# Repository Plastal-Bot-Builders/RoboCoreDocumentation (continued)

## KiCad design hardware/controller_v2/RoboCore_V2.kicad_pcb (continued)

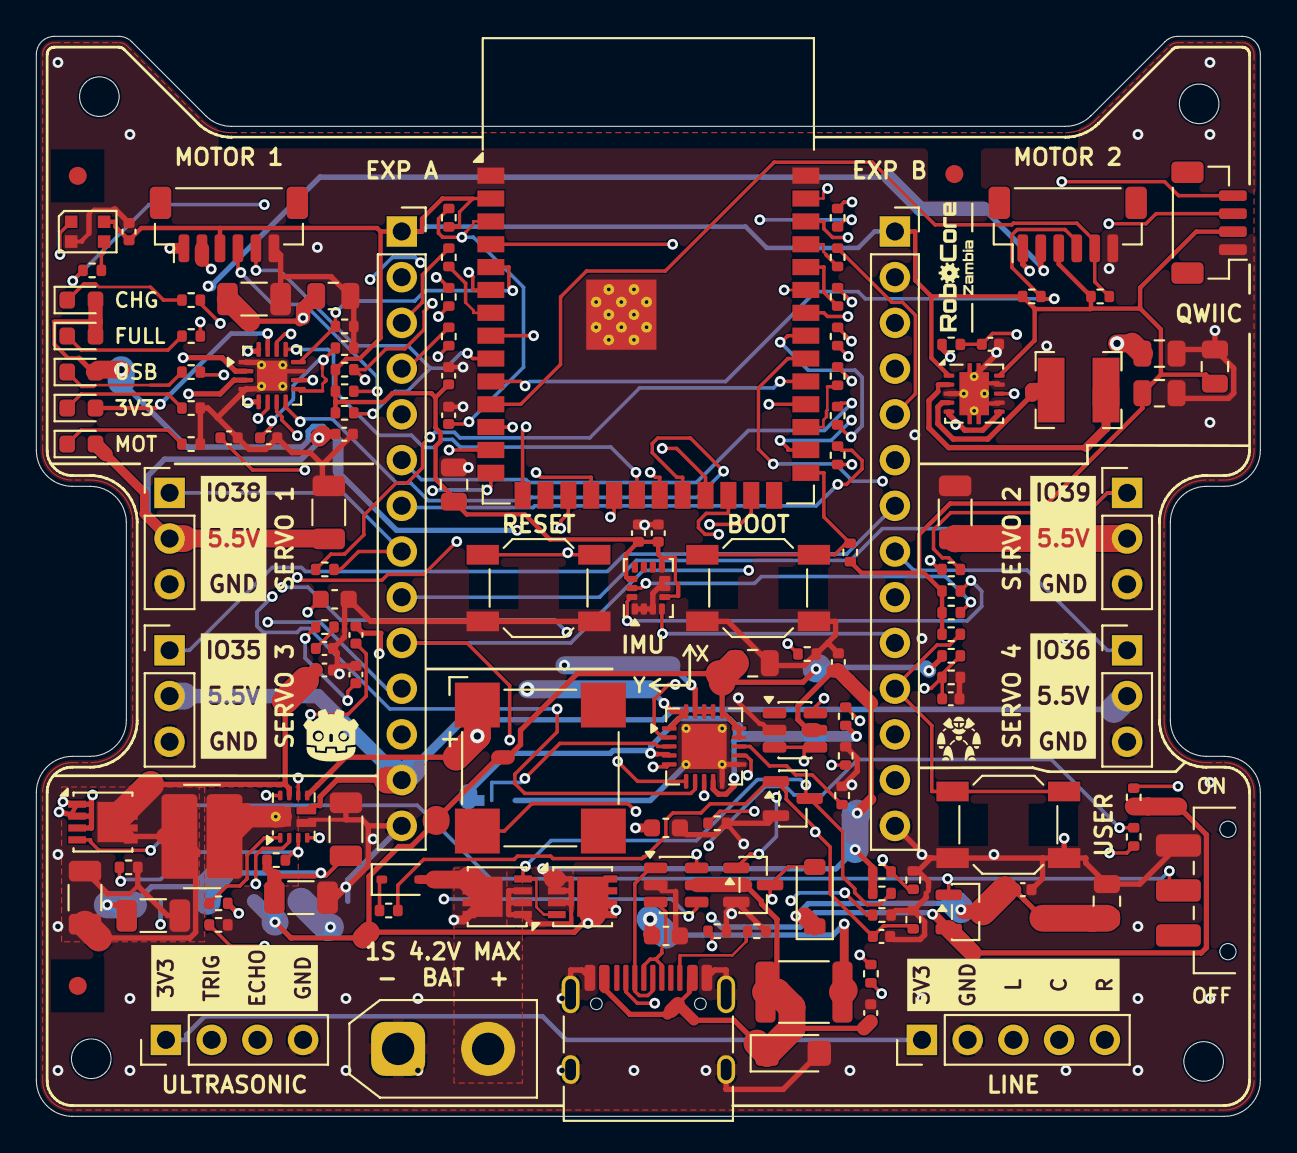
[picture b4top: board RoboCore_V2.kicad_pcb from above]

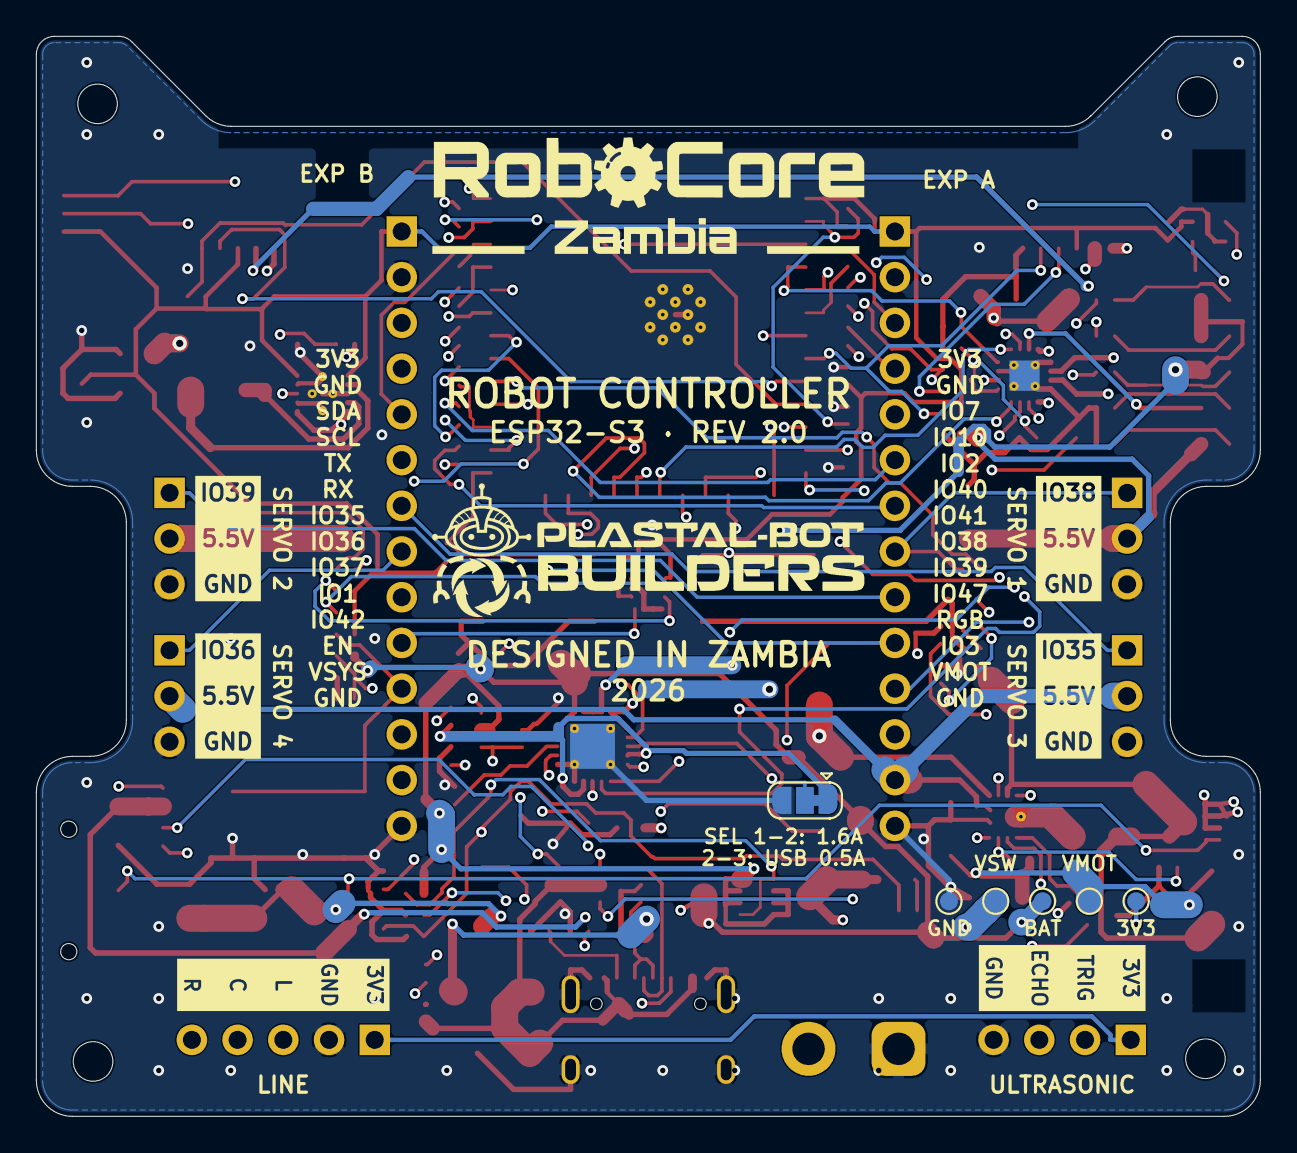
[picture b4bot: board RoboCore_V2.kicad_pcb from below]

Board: 4 copper layers, 68.0 x 60.0 mm, 146 parts (6 on the bottom side), 100 nets.

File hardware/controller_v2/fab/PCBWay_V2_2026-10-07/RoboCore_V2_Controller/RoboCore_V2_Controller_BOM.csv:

Item #,Designator,Qty,Manufacturer,Mfg Part #,Description / Value,Package/Footprint,Mounting Type,LCSC Part #,Notes
1,BZ201,1,Same Sky (CUI),CMT-8504-100-SMT-TR,Magnetic buzzer 8.5 mm (CMT-8504-100-SMT),MagneticBuzzer_CUI_CMT-8504-100-SMT,SMD,C22359707,"LCSC had only 12 (2026-10-07); Digi-Key has 30,000+."
2,"C101,C106,C107,C112,C114,C120,C122,C202,C204,C205,C206,C302",12,Samsung,CL05B104KB5NNNC,Ceramic capacitor 100nF 50V X7R ±10% 0402 (0.1uF),C_0402_1005Metric,SMD,C960916,
3,C102,1,Samsung,CL10A105KA8NNNC,Ceramic capacitor 1uF 25V X5R ±10% 0603 (1uF),C_0603_1608Metric,SMD,C5673,
4,C103,1,Samsung,CL10A106MO8NQNC,Ceramic capacitor 10uF 16V X5R ±20% 0603 (10uF),C_0603_1608Metric,SMD,C92487,
5,C104,1,Samsung,CL21A475KAQNNNE,Ceramic capacitor 4.7uF 25V X5R ±10% 0805 (4.7uF),C_0805_2012Metric,SMD,C1779,
6,"C105,C108,C301",3,Samsung,CL21A106KOQNNNE,Ceramic capacitor 10uF 16V X5R ±10% 0805 (10uF),C_0805_2012Metric,SMD,C1713,
7,"C109,C110,C201",3,Samsung,CL21A226MAQNNNE,Ceramic capacitor 22uF 25V X5R ±20% 0805 (22uF),C_0805_2012Metric,SMD,C45783,
8,"C111,C117,C118,C119,C303,C401,C402",7,Samsung,CL31A226KAHNNNE,Ceramic capacitor 22uF 25V X5R ±10% 1206 (22uF),C_1206_3216Metric,SMD,C12891,
9,C113,1,Samsung,CL10A225KO8NNNC,Ceramic capacitor 2.2uF 16V X5R ±10% 0603 (2.2uF),C_0603_1608Metric,SMD,C23630,
10,C115,1,Samsung,CL05B103KB5NNNC,Ceramic capacitor 10nF 50V X7R ±10% 0402 (10nF),C_0402_1005Metric,SMD,C15195,
11,C116,1,Samsung,CL05C220JB5NNNC,Ceramic capacitor 22pF 50V C0G ±5% 0402 (22pF),C_0402_1005Metric,SMD,C70464,
12,"C121,C203",2,Samsung,CL05A105KA5NNNC,Ceramic capacitor 1uF 25V X5R ±10% 0402 (1uF),C_0402_1005Metric,SMD,C16193167,
13,"C304,C305",2,Samsung,CL05B102KB5NNNC,Ceramic capacitor 1nF 50V X7R ±10% 0402 (1nF),C_0402_1005Metric,SMD,C14442,
14,"D101,D105",2,Lite-On,LTST-C191KRKT,LED red 0603 (RED),LED_0603_1608Metric,SMD,C125099,
15,"D102,D104",2,Lite-On,LTST-C191KGKT,LED green 0603 (GREEN),LED_0603_1608Metric,SMD,C125098,
16,D103,1,Lite-On,LTST-C191TBKT,LED blue 0603 (BLUE),LED_0603_1608Metric,SMD,C99290,
17,D106,1,Littelfuse,SMF5.0A,TVS diode 5 V (SMF5.0A),D_SMF,SMD,C151296,
18,D107,1,Vishay,1N4148WS-E3-08,Switching diode (1N4148WS),D_SOD-323,SMD,C129905,
19,D201,1,Worldsemi,WS2812B-2020-V6,Addressable RGB LED 2020 (WS2812B-2020),LED_WS2812B-2020_PLCC4_2.0x2.0mm,SMD,C52917434,
20,D202,1,Diodes Inc,1N4148W-7-F,Switching diode (1N4148W),D_SOD-123,SMD,C83528,
21,F101,1,Bourns,MF-MSMF150/24X-2,PTC resettable fuse 1.5 A (1.5A),Fuse_1812_4532Metric,SMD,C78695,
22,J101,1,HRO,TYPE-C-31-M-12,"USB-C receptacle, 16 pin (TYPE-C-31-M-12)",USB_C_Receptacle_HRO_TYPE-C-31-M-12,SMD,C165948,
23,J102,1,AMASS,XT30UPB-M,"Battery connector XT30, male, vertical (XT30UPB-M)",AMASS_XT30UPB-M_1x02_P5.0mm_Vertical,THT,C428721,"Through-hole, top side."
24,"J201,J403",2,JST,BM04B-SRSS-TB,JST SH 4-pin vertical header (Qwiic / ULTRASONIC),JST_SH_BM04B-SRSS-TB_1x04-1MP_P1.00mm_Vertical,SMD,C160390,
25,"J301,J302",2,JST,BM06B-SRSS-TB,JST SH 6-pin vertical header (MOTOR_1 / MOTOR_2),JST_SH_BM06B-SRSS-TB_1x06-1MP_P1.00mm_Vertical,SMD,C160392,
26,"J401,J402,J407,J408",4,hanxia,HX PH254-01-03-Z-L11.5,"Pin header 1x3, 2.54 mm, straight (SERVO_1 / SERVO_2 / SERVO_3 / SERVO_4)",PinHeader_1x03_P2.54mm_Vertical,THT,C52016391,"Through-hole, top side, short end in the board (6 mm pin up)."
27,J404,1,JST,BM05B-SRSS-TB,JST SH 5-pin vertical header (LINE_FOLLOWER),JST_SH_BM05B-SRSS-TB_1x05-1MP_P1.00mm_Vertical,SMD,C160391,
28,"J405,J406",2,Hong Cheng,HC-PM254-8.5H-1x14PZ,"Female socket 1x14, 2.54 mm, 8.5 mm tall (EXPANSION_A / EXPANSION_B)",PinSocket_1x14_P2.54mm_Vertical,THT,C22373900,"Through-hole, top side."
29,L101,1,Bourns,SRN4018-2R2M,Power inductor 2.2 uH (2.2uH),L_Bourns-SRN4018,SMD,C913207,
30,L102,1,Bourns,SRP5030CA-2R2M,Power inductor 2.2 uH (2.2uH),L_Bourns_SRP5030CA,SMD,C2046809,
31,Q101,1,Alpha & Omega,AO3401A,P-channel MOSFET 30 V (AO3401A),SOT-23,SMD,C15127,
32,"Q102,Q103,Q104",3,Vishay,SI7655DN-T1-GE3,"P-channel MOSFET, PowerPAK 1212-8 (SI7655DN)",Vishay_PowerPAK_1212-8_Single,SMD,C727830,
33,"Q105,Q201",2,Alpha & Omega,AO3400A,N-channel MOSFET 30 V (AO3400A),SOT-23,SMD,C20917,
34,"R101,R102",2,UNI-ROYAL,0402WGF5101TCE,Chip resistor 5.1kΩ ±1% 0402 (5.1k),R_0402_1005Metric,SMD,C25905,
35,"R103,R106,R201,R202,R203,R303,R304,R305,R306,R307",10,UNI-ROYAL,0402WGF1002TCE,Chip resistor 10kΩ ±1% 0402 (10k),R_0402_1005Metric,SMD,C25744,
36,R104,1,UNI-ROYAL,0402WGF2673TCE,Chip resistor 267kΩ ±1% 0402 (267k),R_0402_1005Metric,SMD,C270622,
37,"R105,R107,R108,R109,R119",5,YAGEO,RC0402FR-071KL,Chip resistor 1kΩ ±1% 0402 (1k),R_0402_1005Metric,SMD,C106235,
38,"R110,R117,R118,R121,R122,R123,R206",7,UNI-ROYAL,0402WGF1003TCE,Chip resistor 100kΩ ±1% 0402 (100k),R_0402_1005Metric,SMD,C25741,
39,"R111,R205",2,YAGEO,RC0402FR-07100RL,Chip resistor 100Ω ±1% 0402 (100),R_0402_1005Metric,SMD,C106232,
40,R112,1,UNI-ROYAL,0402WGF9101TCE,Chip resistor 9.1kΩ ±1% 0402 (9.1k),R_0402_1005Metric,SMD,C25926,
41,"R113,R115",2,UNI-ROYAL,0402WGF3003TCE,Chip resistor 300kΩ ±1% 0402 (300k),R_0402_1005Metric,SMD,C25774,
42,R114,1,UNI-ROYAL,0402WGF8452TCE,Chip resistor 84.5kΩ ±1% 0402 (84.5k),R_0402_1005Metric,SMD,C26988,
43,R116,1,UNI-ROYAL,0402WGF2003TCE,Chip resistor 200kΩ ±1% 0402 (200k),R_0402_1005Metric,SMD,C25764,
44,R120,1,UNI-ROYAL,0402WGF2201TCE,Chip resistor 2.2kΩ ±1% 0402 (2.2k),R_0402_1005Metric,SMD,C25879,
45,R124,1,UNI-ROYAL,0402WGF3303TCE,Chip resistor 330kΩ ±1% 0402 (330k),R_0402_1005Metric,SMD,C25778,
46,R125,1,UNI-ROYAL,0402WGF1004TCE,Chip resistor 1MΩ ±1% 0402 (1M),R_0402_1005Metric,SMD,C26083,
47,R126,1,UNI-ROYAL,0402WGF9532TCE,Chip resistor 95.3kΩ ±1% 0402 (95.3k),R_0402_1005Metric,SMD,C26990,
48,R204,1,YAGEO,RC0402FR-0733RL,Chip resistor 33Ω ±1% 0402 (33),R_0402_1005Metric,SMD,C138002,
49,"R207,R208",2,UNI-ROYAL,0402WGF4701TCE,Chip resistor 4.7kΩ ±1% 0402 (4.7k),R_0402_1005Metric,SMD,C25900,
50,"R301,R302",2,UNI-ROYAL,0402WGF1652TCE,Chip resistor 16.5kΩ ±1% 0402 (16.5k),R_0402_1005Metric,SMD,C25857,
51,"R401,R402,R403,R404,R405,R406,R407,R408,R409,R410,R411,R412,R413",13,UNI-ROYAL,0402WGF3300TCE,Chip resistor 330Ω ±1% 0402 (330),R_0402_1005Metric,SMD,C25104,
52,SW101,1,C&K,JS102011SAQN,"Slide switch SPDT, side-actuated (ON/OFF)",SW_SPDT_CK_JS102011SAQN,SMD,C221660,"LCSC shows 0 stock (2026-10-07); Digi-Key has 54,000+. Lever must overhang the board edge as drawn."
53,"SW201,SW202,SW203",3,Alps Alpine,SKQGADE010,Tactile switch 5.2 x 5.2 mm (RESET / BOOT / USER),SW_SPST_SKQG_WithoutStem,SMD,C116647,
54,U101,1,STMicroelectronics,USBLC6-2SC6,"USB ESD protection, 2 lines (USBLC6-2SC6)",SOT-23-6,SMD,C7519,
55,U102,1,Microchip,MCP73871-2CCI/ML,"Li-ion charger with power path, 4.20 V charge voltage (MCP73871-2CCI/ML)",QFN-20-1EP_4x4mm_P0.5mm_EP2.5x2.5mm_ThermalVias,SMD,C5121473,Must be the -2 version (4.20 V). Other suffixes charge to the wrong voltage.
56,U103,1,Texas Instruments,TPS63001DRCR,"Buck-boost converter, 3.3 V fixed (TPS63001DRCR)",Texas_DRC0010J_ThermalVias,SMD,C28060,
57,U104,1,Texas Instruments,TPS61089RNRR,"Boost converter, 7 A switch (TPS61089RNRR)",Texas_VQFN-RNR0011A-11,SMD,C165129,
58,U105,1,Texas Instruments,TPS3700DDCR,Window voltage supervisor (TPS3700),TSOT-23-6,SMD,C33002,
59,U201,1,Espressif,ESP32-S3-WROOM-1-N8R2,"Wi-Fi/BLE module, 8 MB flash, 2 MB quad PSRAM (ESP32-S3-WROOM-1-N8R2)",ESP32-S3-WROOM-1,SMD,C2913204,Alternative: -N16R2. Do NOT use R8 / R16V (octal PSRAM) versions.
60,U202,1,STMicroelectronics,LSM6DSOXTR,"6-axis IMU (accelerometer + gyroscope), I2C (LSM6DSOX)",LGA-14_3x2.5mm_P0.5mm_LayoutBorder3x4y,SMD,C481766,
61,U301,1,Texas Instruments,DRV8411ARTER,"Dual H-bridge motor driver, 4 A (DRV8411ARTER)",WQFN-16-1EP_3x3mm_P0.5mm_EP1.68x1.68mm_ThermalVias,SMD,C18816315,

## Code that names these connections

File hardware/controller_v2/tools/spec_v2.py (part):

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    notes=[("1S only", 7.62, 48.26), ("trip 4.6 V", 71.12, 78.74)])

# =========================================================================== MCU
GPIO = {1: "GND", 2: "+3V3", 3: "EN", 4: "VBAT_SENSE", 5: "MOTA_ISENSE", 6: "MOTB_ISENSE", 7: "IR_L", 8: "ENC1_A", 9: "ENC1_B",
        10: "ENC2_A", 11: "ENC2_B", 12: "I2C_SDA", 13: "USB_D-", 14: "USB_D+", 15: "EXP_IO3", 17: "I2C_SCL", 18: "IR_C",
        19: "MOTA_IN1", 20: "MOTA_IN2", 21: "MOTB_IN1", 22: "MOTB_IN2", 23: "MOT_NFAULT", 24: "BUZZER", 25: "RGB_DATA",
        27: "BOOT", 28: "SERVO3", 29: "SERVO4", 30: "EXP_IO37", 31: "SERVO1", 32: "SERVO2", 33: "US_TRIG", 34: "US_ECHO",
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        CONN("J201", 4, "Qwiic", "Connector_JST:JST_SH_BM04B-SRSS-TB_1x04-1MP_P1.00mm_Vertical", 86.36, 25.4,
             {1: "GND", 2: "+3V3", 3: "I2C_SDA", 4: "I2C_SCL"}, fields={"MF": "JST", "MP": "BM04B-SRSS-TB"}),
    ],
    label_nets={"I2C_SDA", "I2C_SCL"})

rgb = BLOCK(
    "RGB STATUS LED", [
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        R("R304", "10k", 66.04, 33.02, "+3V3", "ENC1_A"),
        R("R305", "10k", 78.74, 33.02, "+3V3", "ENC1_B"),
    ],
    label_nets={"ENC1_A", "ENC1_B"})

motor2 = BLOCK(
    "MOTOR 2 (XRP JST-SH 6-PIN)", [
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        R("R306", "10k", 66.04, 33.02, "+3V3", "ENC2_A"),
        R("R307", "10k", 78.74, 33.02, "+3V3", "ENC2_B"),
    ],
    label_nets={"ENC2_A", "ENC2_B"})

# =========================================================================== IO CONNECTORS
H = "Connector_PinHeader_2.54mm:PinHeader_1x{:02d}_P2.54mm_Vertical"
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
ultra = BLOCK(
    "ULTRASONIC SENSOR", [
        "HC-SR04-type ultrasonic module on a 4-pin 2.54 mm header: 3V3, TRIG, ECHO, GND (the HC-SR04 pin order,",
        "so a straight cable works). Use a 3.3 V-capable module (HC-SR04+, RCWL-1601). Header again since 2026-10-08."],
    (116.84, 15.24), (101.6, 60.96), [
        CONN("J403", 4, "ULTRASONIC", H.format(4), 50.8, 25.4,
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
exp_a = BLOCK(
    "EXPANSION HEADER A", [
        "Female 2.54 mm header: the sensor, servo, buzzer and LED signals, for prototyping."],
    (15.24, 81.28), (96.52, 76.2), [
        CONN("J405", 14, "EXPANSION_A", S.format(14), 50.8, 22.86,
             {1: "+3V3", 2: "GND", 3: "IR_L_HDR", 4: "IR_C_HDR", 5: "IR_R_HDR", 6: "US_TRIG_HDR", 7: "US_ECHO_HDR", 8: "SERVO1_HDR", 9: "SERVO2_HDR",
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
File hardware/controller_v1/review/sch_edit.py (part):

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        {"1": "PWR_EN_N", "2": GNDc}, ROOT, "Connector_JST:JST_PH_B2B-PH-K_1x02_P2.00mm_Vertical",
        "http://www.jst-mfg.com/product/pdf/eng/ePH.pdf", "External ON/OFF switch (closed = ON); fit a jumper for always-on",
        {"MF": "JST", "MP": "B2B-PH-K-S"})
R.flag(142.24, 41.91, ROOT)   # VSYS_SW is driven through Q3 (passive pins)
for t_, x_, y_ in (("MOTOR SUPPLY BOOST 3.0-4.2 V -> 6 V (TPS61089, 5 A limit)", 299.72, 30.48),
                   ("Boost passives (values per TI SLVSD38C)", 299.72, 80.01),
                   ("POWER SWITCH: chassis switch on J5, closed = ON (charger stays live when OFF)", 299.72, 142.24),
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S = E.S
def relabel(ed, item, new):
    ed.replace_block(item, item["block"].replace('"%s"' % item["name"], '"%s"' % new, 1))
relabel(E, E.label_at("BOOT", 30.48, 45.72), "VBAT_SENSE")        # IO0 -> battery voltage (ADC1_CH0)
relabel(E, E.label_at("BOOT", 152.4, 175.26), "I2C_SCL")          # BOOT button + auto-boot transistor -> IO9
relabel(E, E.label_at("nFAULT_B", 30.48, 60.96), "nSLEEP")        # IO6 -> driver nSLEEP
relabel(E, E.label_at("nFAULT_B", 151.13, 151.13), "nSLEEP")
sh = next(x for x in S.sheets if x["name"] == "MotorDriver")
E.replace_block(sh, sh["block"].replace('(pin "nFAULT_B" input', '(pin "nSLEEP" input', 1))
# --- CP2102N QFN20 -> QFN24 (same drawing for shared pins; DTR now exists)
u2 = S.sym("U2"); lb24 = E.need("Interface_USB", "CP2102N-Axx-xQFN24")
p24 = pin_points(lb24, u2["x"], u2["y"], u2["rot"])
b = u2["block"].replace('(lib_id "Interface_USB:CP2102N-Axx-xQFN20")', '(lib_id "Interface_USB:CP2102N-Axx-xQFN24")')
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b = re.sub(r'(\(property "Description" )"[^"]*"', r'\1"USB to UART bridge with DTR (auto-program), QFN-24"', b, count=1)
E.replace_block(u2, b)
P = lambda n: p24[n][0]
dtr = E.label_at("DTR", 217.17, 54.61)
E.replace_block(dtr, dtr["block"].replace("(at 217.17 54.61 0)", "(at %s %s 0)" % (f(P("23")[0]), f(P("23")[1]))))
for n in ("1", "22", "18"): E.add.append(nc(*P(n)[:2]))                       # RI/CLK, DSR, CTS unused
for x, y in ((217.17, 80.01), (217.17, 77.47)): E.delete(E.nc_at(x, y))       # now RXT / TXT
# LED wires used to end on old TXT/RXT pins (now GPIO.2 / GPIO.3): shorten and relabel
for oldy, net, newpin in ((82.55, "CP_TXT", "14"), (85.09, "CP_RXT", "13")):
    w = next(w for w in S.wires if any(abs(px - 217.17) < .01 and abs(py - oldy) < .01 for px, py in w["pts"]))
    (x1, y1), (x2, y2) = w["pts"][0], w["pts"][-1]
    assert abs(y1 - y2) < .01, ("LED wire not horizontal", w["pts"])
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
# ======================================================================= Motor driver sheet
M = Ed(D + "/MotorDriver.kicad_sch"); S = M.S
relabel(M, next(l for l in S.labels if l["name"] == "nFAULT_B"), "nFAULT_A")   # both drivers share one open-drain fault line
M.add.append(label("nSLEEP", 104.14, 60.96, 180, "hierarchical_label", "input"))
M.add.append(label("nSLEEP", 97.79, 143.51, 180, "hierarchical_label", "input"))
M.need("power", "+6V")
for ref in ("#PWR039", "#PWR043"):
    p = S.sym(ref); b = p["block"].replace('(lib_id "power:+BATT")', '(lib_id "power:+6V")')
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
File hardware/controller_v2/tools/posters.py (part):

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        ("USB-C", "HRO TYPE-C-31-M-12 + ESD", "Charging and programming"),
        ("Lights", "WS2812B-2020-V6 RGB + 5 status LEDs", "CHG, FULL, USB, 3V3, MOT"),
        ("Sound / buttons", "CMT-8504 buzzer; RESET, BOOT, USER", "PWM tones; USER on IO42"),
        ("Ports", "Qwiic (I2C), 2 × 14-pin expansion", "3.3 V, VMOT, switched battery, spare GPIOs, UART, I2C"),
    ]
    body = f"""
<div class="col" style="flex:1.25">{img(R/'v2_top.png', '<b>Top side</b> — all SMD parts are on top; white knockout boxes carry the pin names of every header (servos, ultrasonic, line follower, battery)')}</div>
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        ("J405 / J406", "Expansion A / B", "1×14 female ×2", "See the pin order table"),
        ("J201", "Qwiic", "JST SH 4", "GND, 3V3, SDA, SCL"),
        ("J102", "Battery", "XT30", "1S Li-ion only, 4.2 V max; 1S2P/3P/4P packs need no change"),
        ("J101", "USB-C", "16-pin", "Charging + programming"),
        ("JP101", "Charge current", "solder jumper (back)", "1-2 adapter 1.65 A (default), 2-3 USB 500 mA"),
        ("TP101–105", "Test pads (back)", "", "3V3, BAT, GND and rails"),
    ]
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            ("IO13 / IO14", "Motor 2 IN1 / IN2"), ("IO15 / IO16", "Encoder 1 A / B"), ("IO17 / IO18", "Encoder 2 A / B"),
            ("IO19 / IO20", "USB D− / D+"), ("IO21", "Motor driver nFAULT"), ("IO35 / IO36", "Servo 3 / 4"), ("IO37", "Expansion B"),
            ("IO38 / IO39", "Servo 1 / 2"), ("IO40 / IO41", "Ultrasonic TRIG / ECHO"), ("IO42", "USER button"),
            ("IO43 / IO44", "UART TX / RX → expansion"), ("IO47", "Buzzer (PWM)"), ("IO48", "WS2812 RGB LED"), ("IO45 / IO46", "strapping pins, unused")]
    body = f"""
<div class="col" style="flex:1.05">{img(R/'v2_bottom.png', '<b>Bottom side</b> — artwork, test pads, charge-current jumper JP101 and the pin names of both expansion headers')}
<div class="note">IR inputs use ADC1, which keeps working with Wi-Fi on. IMU axes: +X towards the top edge, +Y towards the left edge (firmware remaps).</div></div>
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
